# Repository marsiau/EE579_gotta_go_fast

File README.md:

# EE579_gotta_go_fast
Repository for EE579 line avoiding car project.

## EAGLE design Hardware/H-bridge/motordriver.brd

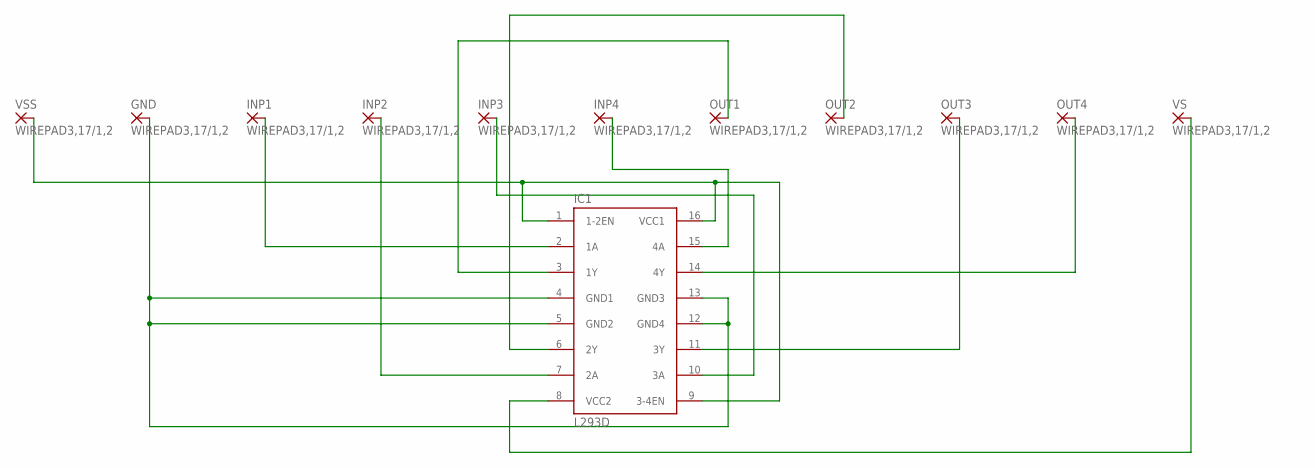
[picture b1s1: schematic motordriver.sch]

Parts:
GND: WIREPAD3,17/1,2; 3,17/1,2
IC1: L293D; DIL16
INP1, INP2, INP3, INP4: WIREPAD3,17/1,2; 3,17/1,2
OUT1, OUT2, OUT3, OUT4: WIREPAD3,17/1,2; 3,17/1,2
VS: WIREPAD3,17/1,2; 3,17/1,2
VSS: WIREPAD3,17/1,2; 3,17/1,2

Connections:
unnamed: IC1.8 (VCC2), VS.1
unnamed: IC1.1 (1-2EN), IC1.9 (3-4EN), IC1.16 (VCC1), VSS.1
unnamed: IC1.15 (4A), INP4.1
unnamed: IC1.14 (4Y), OUT4.1
unnamed: GND.1, IC1.4 (GND1), IC1.5 (GND2), IC1.12 (GND4), IC1.13 (GND3)
unnamed: IC1.11 (3Y), OUT3.1
unnamed: IC1.10 (3A), INP3.1
unnamed: IC1.2 (1A), INP1.1
unnamed: IC1.7 (2A), INP2.1
unnamed: IC1.3 (1Y), OUT1.1
unnamed: IC1.6 (2Y), OUT2.1

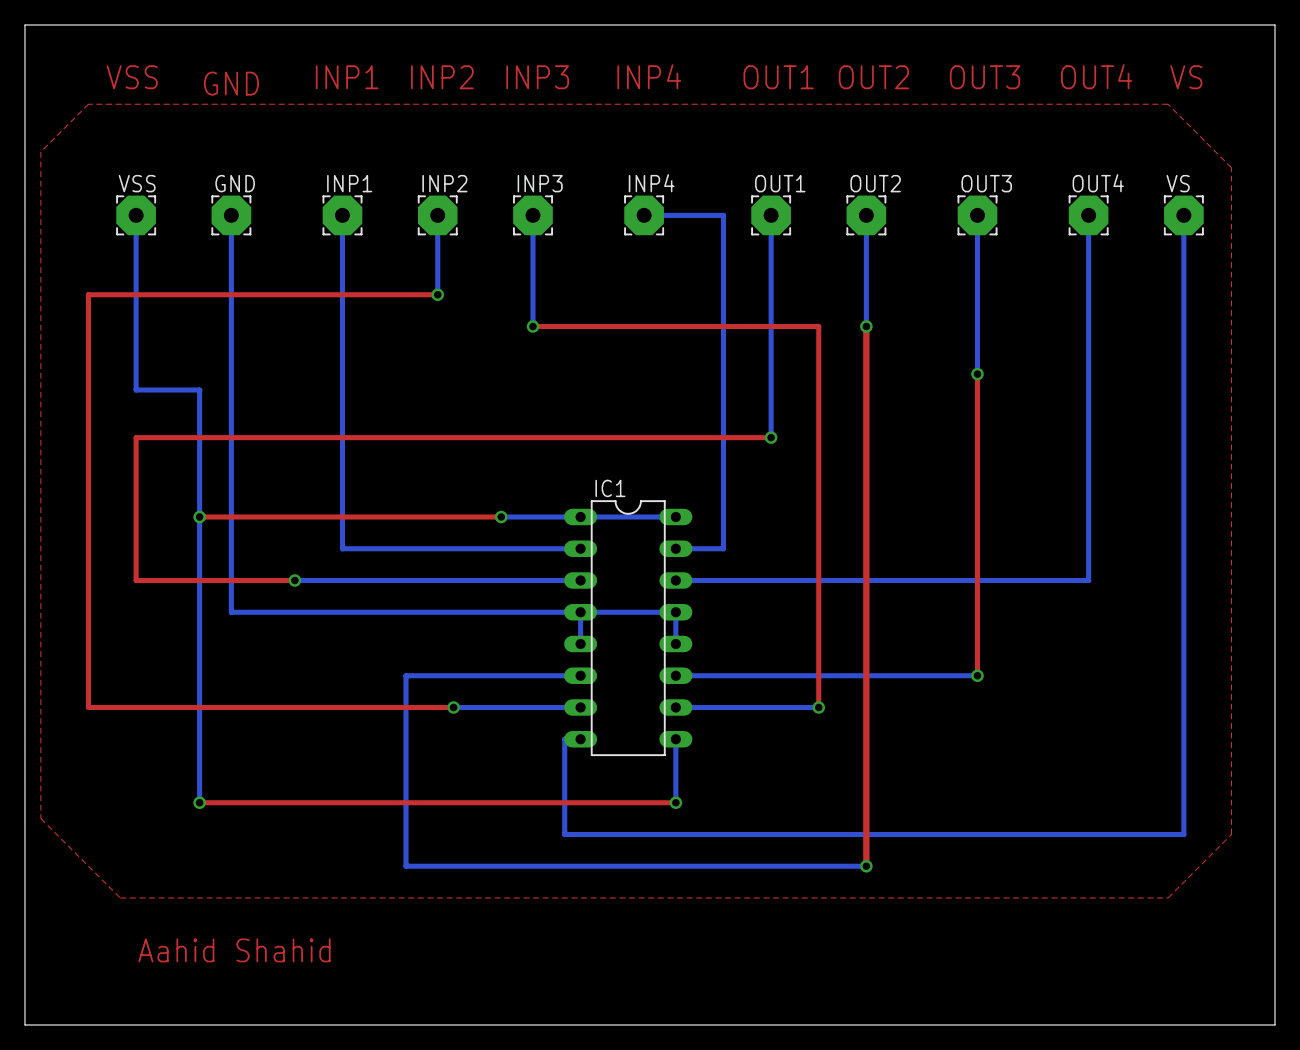
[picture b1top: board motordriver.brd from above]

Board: 2 copper layers, 100.0 x 80.0 mm, 12 parts (0 on the bottom side), 11 nets.

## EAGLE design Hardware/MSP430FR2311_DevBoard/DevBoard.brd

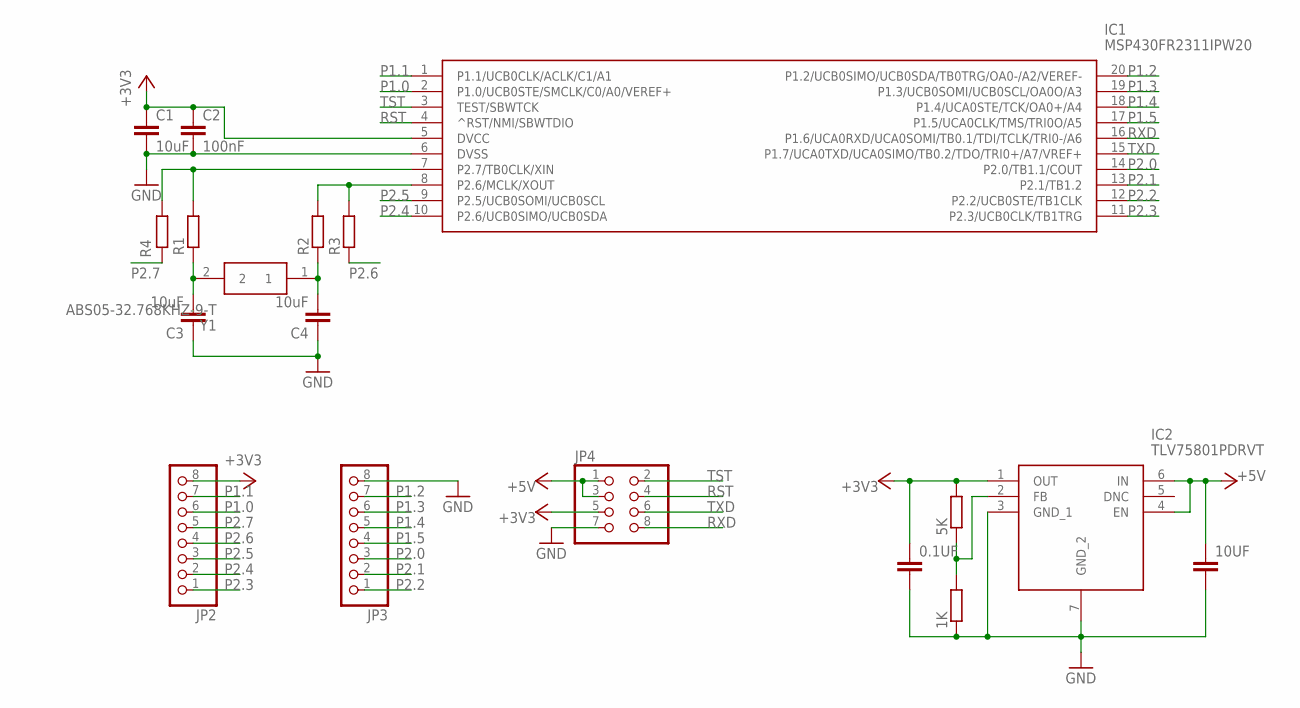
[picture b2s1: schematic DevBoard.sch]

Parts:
0.1UF, 10UF: C-EUC0805K; C0805K
1K, 5K: R-EU_R0805; R0805
C1, C3, C4: 10uF; C0805K
C2: 100nF; C0805K
IC1: MSP430FR2311IPW20; SOP65P640X120-20N
IC2: TLV75801PDRVT; SON65P200X200X80-7N
JP2, JP3: PINHD-1X8; 1X08
JP4: PINHD-2X4; 2X04
R1, R2, R3, R4: R-EU_R0402; R0402
Y1: ABS05-32.768KHZ-9-T; ABS05

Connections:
+3V3: 0.1UF.1, 5K.2, C1.1, C2.1, IC1.5 (DVCC), IC2.1 (OUT), JP2.8, JP4.5
+5V: 10UF.1, IC2.4 (EN), IC2.6 (IN), JP4.1, JP4.3
GND: 0.1UF.2, 1K.1, 10UF.2, C1.2, C2.2, C3.1, C4.1, IC1.6 (DVSS), IC2.3 (GND_1), IC2.7 (GND_2), JP3.8, JP4.7
unnamed: C3.2, R1.1, Y1.2
unnamed: C4.2, R2.1, Y1.1
unnamed: IC1.7 (P2.7/TB0CLK/XIN), R1.2, R4.1
unnamed: IC1.8 (P2.6/MCLK/XOUT), R2.2, R3.2
unnamed: 1K.2, 5K.1, IC2.2 (FB)
P1.0: IC1.2 (P1.0/UCB0STE/SMCLK/C0/A0/VEREF+), JP2.6
P1.1: IC1.1 (P1.1/UCB0CLK/ACLK/C1/A1), JP2.7
P1.2: IC1.20 (P1.2/UCB0SIMO/UCB0SDA/TB0TRG/OA0-/A2/VE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), JP3.7
P1.3: IC1.19 (P1.3/UCB0SOMI/UCB0SCL/OA0O/A3), JP3.6
P1.4: IC1.18 (P1.4/UCA0STE/TCK/OA0+/A4), JP3.5
P1.5: IC1.17 (P1.5/UCA0CLK/TMS/TRI0O/A5), JP3.4
P2.0: IC1.14 (P2.0/TB1.1/COUT), JP3.3
P2.1: IC1.13 (P2.1/TB1.2), JP3.2
P2.2: IC1.12 (P2.2/UCB0STE/TB1CLK), JP3.1
P2.3: IC1.11 (P2.3/UCB0CLK/TB1TRG), JP2.1
P2.4: IC1.10 (P2.6/UCB0SIMO/UCB0SDA), JP2.2
P2.5: IC1.9 (P2.5/UCB0SOMI/UCB0SCL), JP2.3
P2.6: JP2.4, R3.1
P2.7: JP2.5, R4.2
RST: IC1.4 (^RST/NMI/SBWTDIO), JP4.4
RXD: IC1.16 (P1.6/UCA0RXD/UCA0SOMI/TB0.1/TDI/TCLK/TR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), JP4.8
TST: IC1.3 (TEST/SBWTCK), JP4.2
TXD: IC1.15 (P1.7/UCA0TXD/UCA0SIMO/TB0.2/TDO/TRI0+/A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), JP4.6

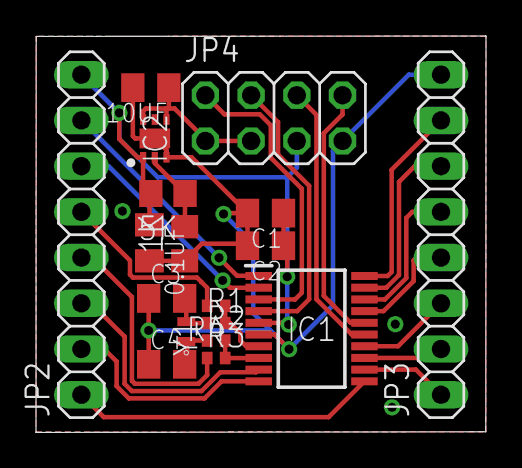
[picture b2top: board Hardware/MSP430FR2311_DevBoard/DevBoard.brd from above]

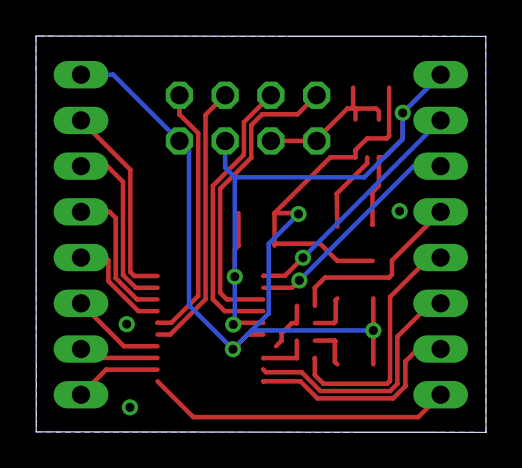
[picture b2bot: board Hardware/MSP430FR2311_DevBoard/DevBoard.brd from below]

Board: 2 copper layers, 25.0 x 22.0 mm, 26 parts (2 on the bottom side), 26 nets.

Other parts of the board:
U$1, U$2, U$3, U$4, U$5, U$7, U$8, U$9: METRIC_15

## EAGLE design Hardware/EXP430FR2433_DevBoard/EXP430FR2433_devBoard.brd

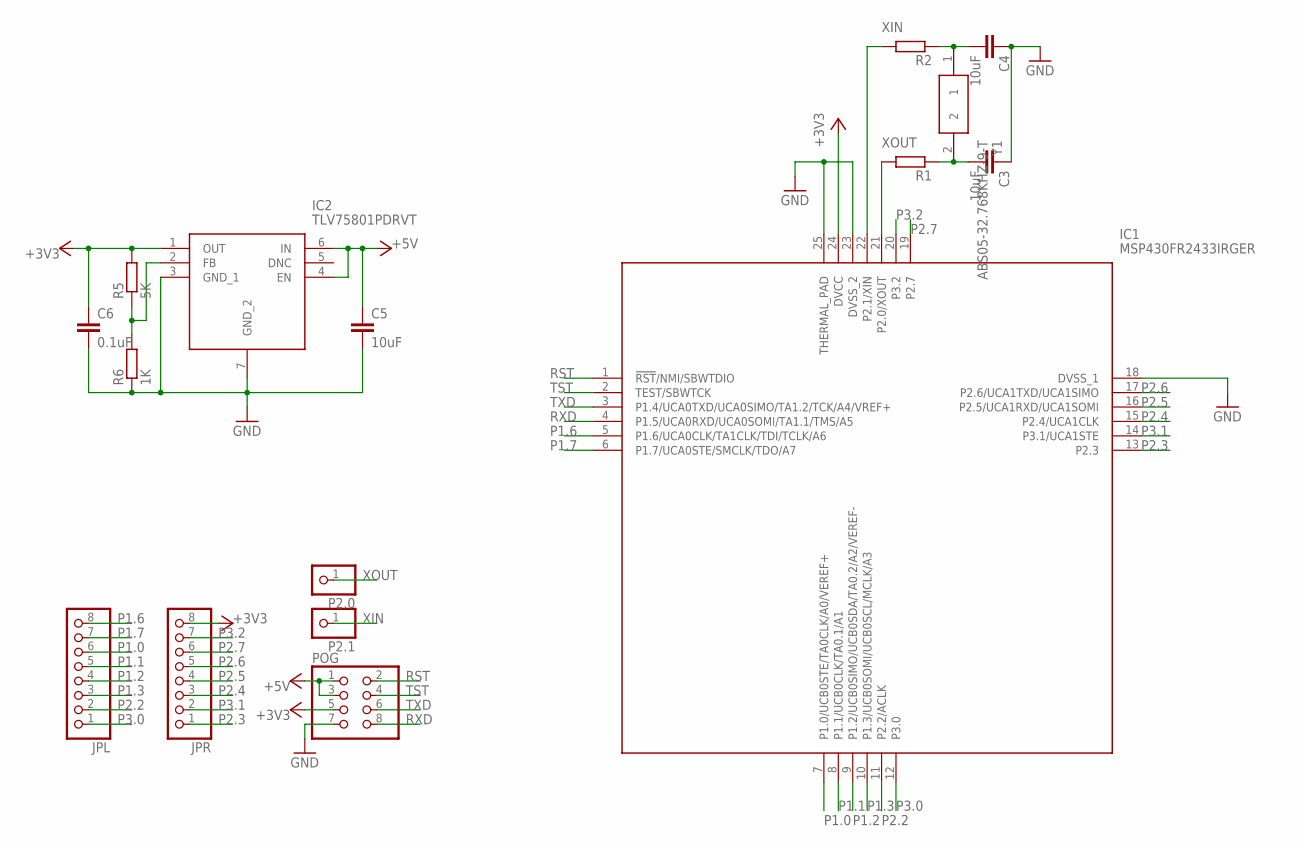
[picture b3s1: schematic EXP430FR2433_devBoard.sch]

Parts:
C3, C4, C5: 10uF; C0805K
C6: 0.1uF; C0805K
IC1: MSP430FR2433IRGER; QFN50P400X400X100-25N
IC2: TLV75801PDRVT; SON65P200X200X80-7N
JPL: PINHD-1X8; 1X08
JPR: PINHD-1X8; 1X08
P2.0, P2.1: PINHD-1X1; 1X01
POG: PINHD-2X4; 2X04
R1, R2: R-EU_R0402; R0402
R5: 5K; R0805
R6: 1K; R0805
Y1: ABS05-32.768KHZ-9-T; ABS05

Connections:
+3V3: C6.1, IC1.24 (DVCC), IC2.1 (OUT), JPR.8, POG.5, R5.2
+5V: C5.1, IC2.4 (EN), IC2.6 (IN), POG.1, POG.3
GND: C3.1, C4.1, C5.2, C6.2, IC1.18 (DVSS_1), IC1.23 (DVSS_2), IC1.25 (THERMAL_PAD), IC2.3 (GND_1), IC2.7 (GND_2), POG.7, R6.1
unnamed: C3.2, R1.1, Y1.2
unnamed: C4.2, R2.1, Y1.1
unnamed: IC2.2 (FB), R5.1, R6.2
P1.0: IC1.7 (P1.0/UCB0STE/TA0CLK/A0/VEREF+), JPL.6
P1.1: IC1.8 (P1.1/UCB0CLK/TA0.1/A1), JPL.5
P1.2: IC1.9 (P1.2/UCB0SIMO/UCB0SDA/TA0.2/A2/VEREF-), JPL.4
P1.3: IC1.10 (P1.3/UCB0SOMI/UCB0SCL/MCLK/A3), JPL.3
P1.6: IC1.5 (P1.6/UCA0CLK/TA1CLK/TDI/TCLK/A6), JPL.8
P1.7: IC1.6 (P1.7/UCA0STE/SMCLK/TDO/A7), JPL.7
P2.2: IC1.11 (P2.2/ACLK), JPL.2
P2.3: IC1.13 (P2.3), JPR.1
P2.4: IC1.15 (P2.4/UCA1CLK), JPR.3
P2.5: IC1.16 (P2.5/UCA1RXD/UCA1SOMI), JPR.4
P2.6: IC1.17 (P2.6/UCA1TXD/UCA1SIMO), JPR.5
P2.7: IC1.19 (P2.7), JPR.6
P3.0: IC1.12 (P3.0), JPL.1
P3.1: IC1.14 (P3.1/UCA1STE), JPR.2
P3.2: IC1.20 (P3.2), JPR.7
RST: IC1.1 (!RST!/NMI/SBWTDIO), POG.2
RXD: IC1.4 (P1.5/UCA0RXD/UCA0SOMI/TA1.1/TMS/A5), POG.8
TST: IC1.2 (TEST/SBWTCK), POG.4
TXD: IC1.3 (P1.4/UCA0TXD/UCA0SIMO/TA1.2/TCK/A4/VREF+), POG.6
XIN: IC1.22 (P2.1/XIN), P2.1.1, R2.2
XOUT: IC1.21 (P2.0/XOUT), P2.0.1, R1.2

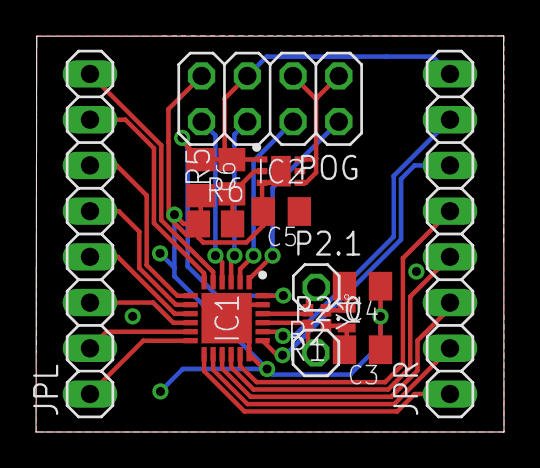
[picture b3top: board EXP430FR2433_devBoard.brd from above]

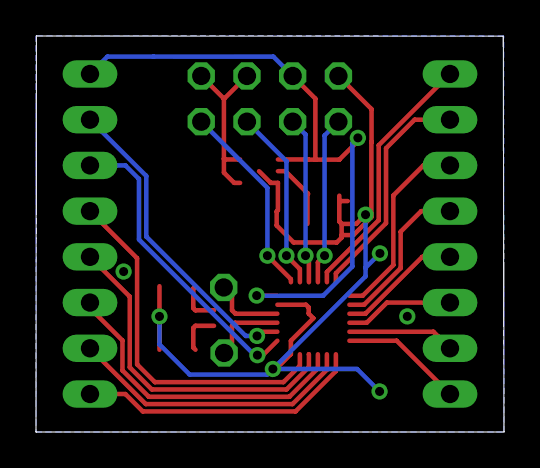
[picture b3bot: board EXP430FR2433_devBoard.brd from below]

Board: 2 copper layers, 26.0 x 22.0 mm, 23 parts (6 on the bottom side), 27 nets.

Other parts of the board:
U$1, U$2, U$3, U$4, U$5, U$6, U$7: METRIC_15

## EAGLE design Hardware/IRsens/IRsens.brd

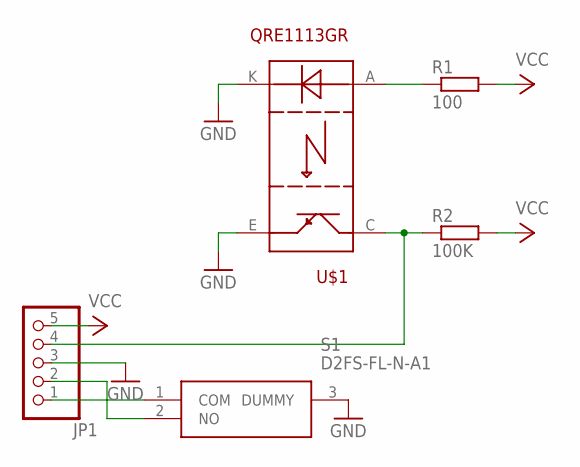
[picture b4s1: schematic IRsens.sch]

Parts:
JP1: PINHD-1X5; 1X05
R1: 100; R0805
R2: 100K; R0805
S1: D2FS-FL-N-A1
U$1: QRE1113GR; 4LEADSMD

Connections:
GND: JP1.3, S1.3 (DUMMY), U$1.E, U$1.K
unnamed: R1.1, U$1.A
unnamed: JP1.4, R2.1, U$1.C
unnamed: JP1.2, S1.2 (NO)
unnamed: JP1.1, S1.1 (COM)
VCC: JP1.5, R1.2, R2.2

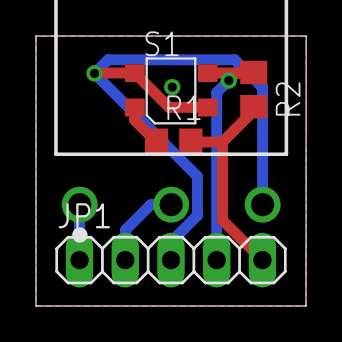
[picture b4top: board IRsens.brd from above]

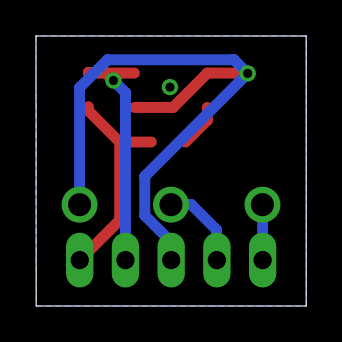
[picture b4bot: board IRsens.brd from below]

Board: 2 copper layers, 15.0 x 15.0 mm, 10 parts (3 on the bottom side), 6 nets.

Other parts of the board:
U$2, U$3, U$4, U$5, U$6: METRIC_15

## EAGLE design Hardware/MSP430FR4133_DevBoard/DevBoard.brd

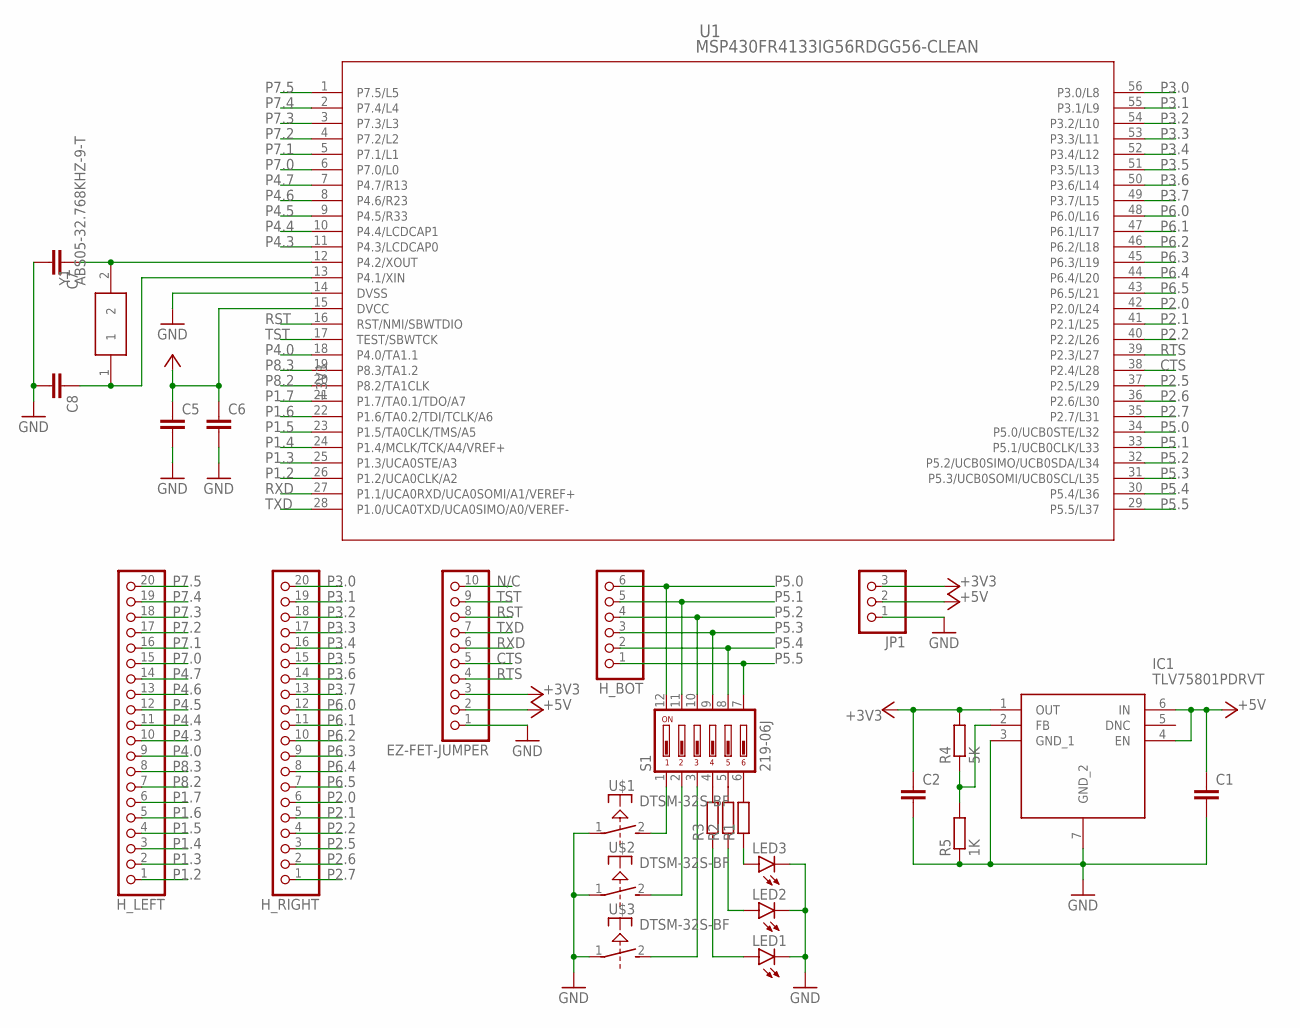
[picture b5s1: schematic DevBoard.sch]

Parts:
C1, C2, C5, C6, C7, C8: C-EUC0805K; C0805K
EZ-FET-JUMPER: PINHD-1X10; 1X10
H_BOT: PINHD-1X6; 1X06
H_LEFT: PINHD-1X20; 1X20
H_RIGHT: PINHD-1X20; 1X20
IC1: TLV75801PDRVT; SON65P200X200X80-7N
JP1: PINHD-1X3; 1X03
LED1, LED2, LED3: LEDCHIP-LED0805; CHIP-LED0805
R1, R2, R3: R-EU_R0805; R0805
R4: 5K; R0805
R5: 1K; R0805
S1: 219-06J; CTS-219-06J
U1: MSP430FR4133IG56RDGG56-CLEAN; DGG56_CLEAN
U$1, U$2, U$3: DTSM-32S-BF; DTSM32SBF
Y1: ABS05-32.768KHZ-9-T; ABS05

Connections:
+3V3: C2.1, C5.1, C6.1, EZ-FET-JUMPER.3, IC1.1 (OUT), JP1.3, R4.2, U1.15 (DVCC)
+5V: C1.1, EZ-FET-JUMPER.2, IC1.4 (EN), IC1.6 (IN), JP1.2
CTS: EZ-FET-JUMPER.5, U1.38 (P2.4/L28)
GND: C1.2, C2.2, C5.2, C6.2, C7.2, C8.2, EZ-FET-JUMPER.1, IC1.3 (GND_1), IC1.7 (GND_2), JP1.1, LED1.C, LED2.C, LED3.C, R5.1, U1.14 (DVSS), U$1.1, U$2.1, U$3.1
unnamed: R1.2, S1.6
unnamed: R2.2, S1.5
unnamed: R3.2, S1.4
unnamed: LED1.A, R3.1
unnamed: LED2.A, R2.1
unnamed: LED3.A, R1.1
unnamed: S1.1, U$1.2 (S)
unnamed: S1.2, U$2.2 (S)
unnamed: S1.3, U$3.2 (S)
unnamed: IC1.2 (FB), R4.1, R5.2
unnamed: C8.1, U1.13 (P4.1/XIN), Y1.1
unnamed: C7.1, U1.12 (P4.2/XOUT), Y1.2
N/C: EZ-FET-JUMPER.10
P1.2: H_LEFT.1, U1.26 (P1.2/UCA0CLK/A2)
P1.3: H_LEFT.2, U1.25 (P1.3/UCA0STE/A3)
P1.4: H_LEFT.3, U1.24 (P1.4/MCLK/TCK/A4/VREF+)
P1.5: H_LEFT.4, U1.23 (P1.5/TA0CLK/TMS/A5)
P1.6: H_LEFT.5, U1.22 (P1.6/TA0.2/TDI/TCLK/A6)
P1.7: H_LEFT.6, U1.21 (P1.7/TA0.1/TDO/A7)
P2.0: H_RIGHT.6, U1.42 (P2.0/L24)
P2.1: H_RIGHT.5, U1.41 (P2.1/L25)
P2.2: H_RIGHT.4, U1.40 (P2.2/L26)
P2.5: H_RIGHT.3, U1.37 (P2.5/L29)
P2.6: H_RIGHT.2, U1.36 (P2.6/L30)
P2.7: H_RIGHT.1, U1.35 (P2.7/L31)
P3.0: H_RIGHT.20, U1.56 (P3.0/L8)
P3.1: H_RIGHT.19, U1.55 (P3.1/L9)
P3.2: H_RIGHT.18, U1.54 (P3.2/L10)
P3.3: H_RIGHT.17, U1.53 (P3.3/L11)
P3.4: H_RIGHT.16, U1.52 (P3.4/L12)
P3.5: H_RIGHT.15, U1.51 (P3.5/L13)
P3.6: H_RIGHT.14, U1.50 (P3.6/L14)
P3.7: H_RIGHT.13, U1.49 (P3.7/L15)
P4.0: H_LEFT.9, U1.18 (P4.0/TA1.1)
P4.3: H_LEFT.10, U1.11 (P4.3/LCDCAP0)
P4.4: H_LEFT.11, U1.10 (P4.4/LCDCAP1)
P4.5: H_LEFT.12, U1.9 (P4.5/R33)
P4.6: H_LEFT.13, U1.8 (P4.6/R23)
P4.7: H_LEFT.14, U1.7 (P4.7/R13)
P5.0: H_BOT.6, S1.12, U1.34 (P5.0/UCB0STE/L32)
P5.1: H_BOT.5, S1.11, U1.33 (P5.1/UCB0CLK/L33)
P5.2: H_BOT.4, S1.10, U1.32 (P5.2/UCB0SIMO/UCB0SDA/L34)
P5.3: H_BOT.3, S1.9, U1.31 (P5.3/UCB0SOMI/UCB0SCL/L35)
P5.4: H_BOT.2, S1.8, U1.30 (P5.4/L36)
P5.5: H_BOT.1, S1.7, U1.29 (P5.5/L37)
P6.0: H_RIGHT.12, U1.48 (P6.0/L16)
P6.1: H_RIGHT.11, U1.47 (P6.1/L17)
P6.2: H_RIGHT.10, U1.46 (P6.2/L18)
P6.3: H_RIGHT.9, U1.45 (P6.3/L19)
P6.4: H_RIGHT.8, U1.44 (P6.4/L20)
P6.5: H_RIGHT.7, U1.43 (P6.5/L21)
P7.0: H_LEFT.15, U1.6 (P7.0/L0)
P7.1: H_LEFT.16, U1.5 (P7.1/L1)
P7.2: H_LEFT.17, U1.4 (P7.2/L2)
P7.3: H_LEFT.18, U1.3 (P7.3/L3)
P7.4: H_LEFT.19, U1.2 (P7.4/L4)
P7.5: H_LEFT.20, U1.1 (P7.5/L5)
P8.2: H_LEFT.7, U1.20 (P8.2/TA1CLK)
P8.3: H_LEFT.8, U1.19 (P8.3/TA1.2)
RST: EZ-FET-JUMPER.8, U1.16 (RST/NMI/SBWTDIO)
RTS: EZ-FET-JUMPER.4, U1.39 (P2.3/L27)
RXD: EZ-FET-JUMPER.6, U1.27 (P1.1/UCA0RXD/UCA0SOMI/A1/VEREF+)
TST: EZ-FET-JUMPER.9, U1.17 (TEST/SBWTCK)
TXD: EZ-FET-JUMPER.7, U1.28 (P1.0/UCA0TXD/UCA0SIMO/A0/VEREF-)

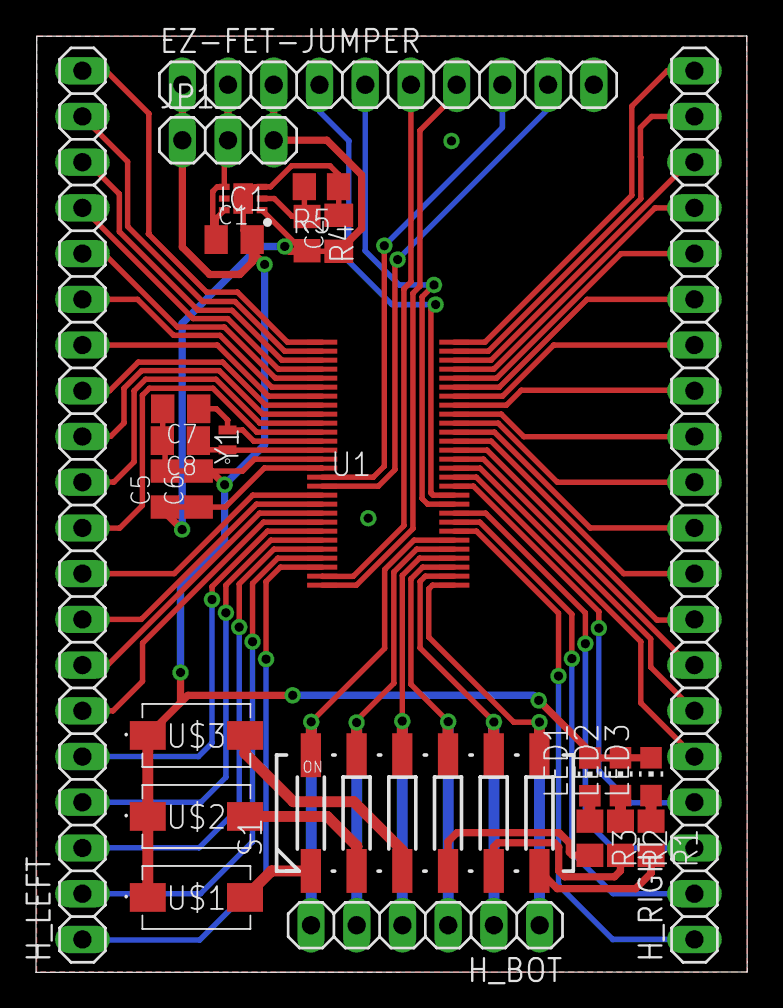
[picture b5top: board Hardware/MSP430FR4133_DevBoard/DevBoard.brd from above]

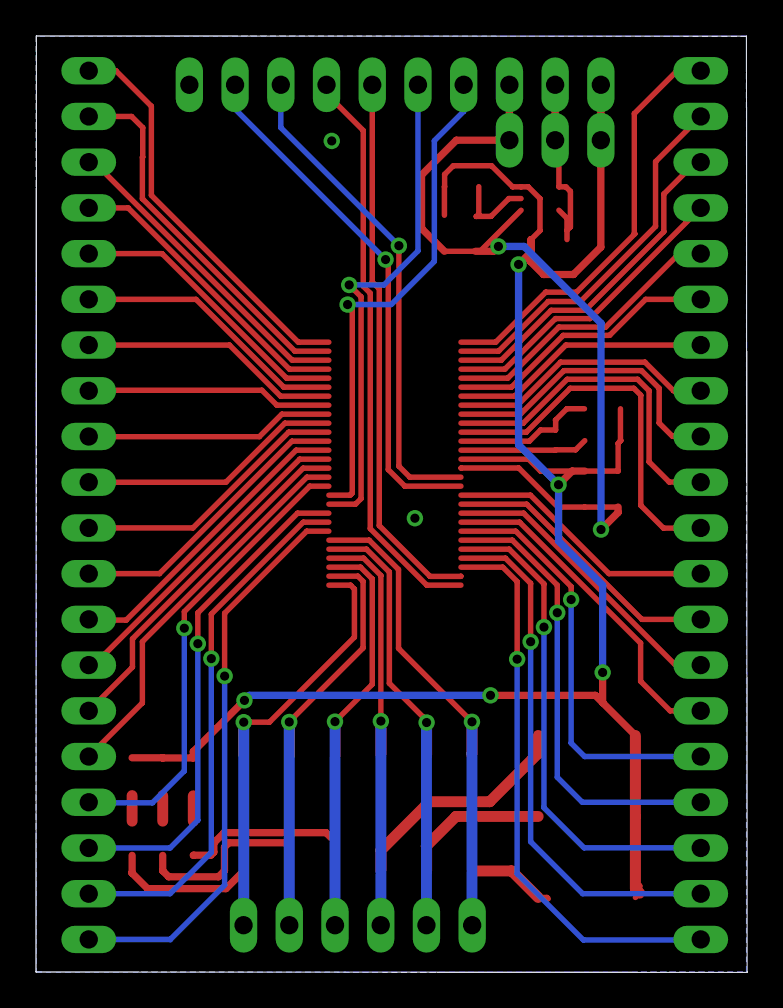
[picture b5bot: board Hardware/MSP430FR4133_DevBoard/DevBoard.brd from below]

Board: 2 copper layers, 39.5 x 52.0 mm, 29 parts (2 on the bottom side), 67 nets.

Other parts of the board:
U$4, U$5, U$6: METRIC_15

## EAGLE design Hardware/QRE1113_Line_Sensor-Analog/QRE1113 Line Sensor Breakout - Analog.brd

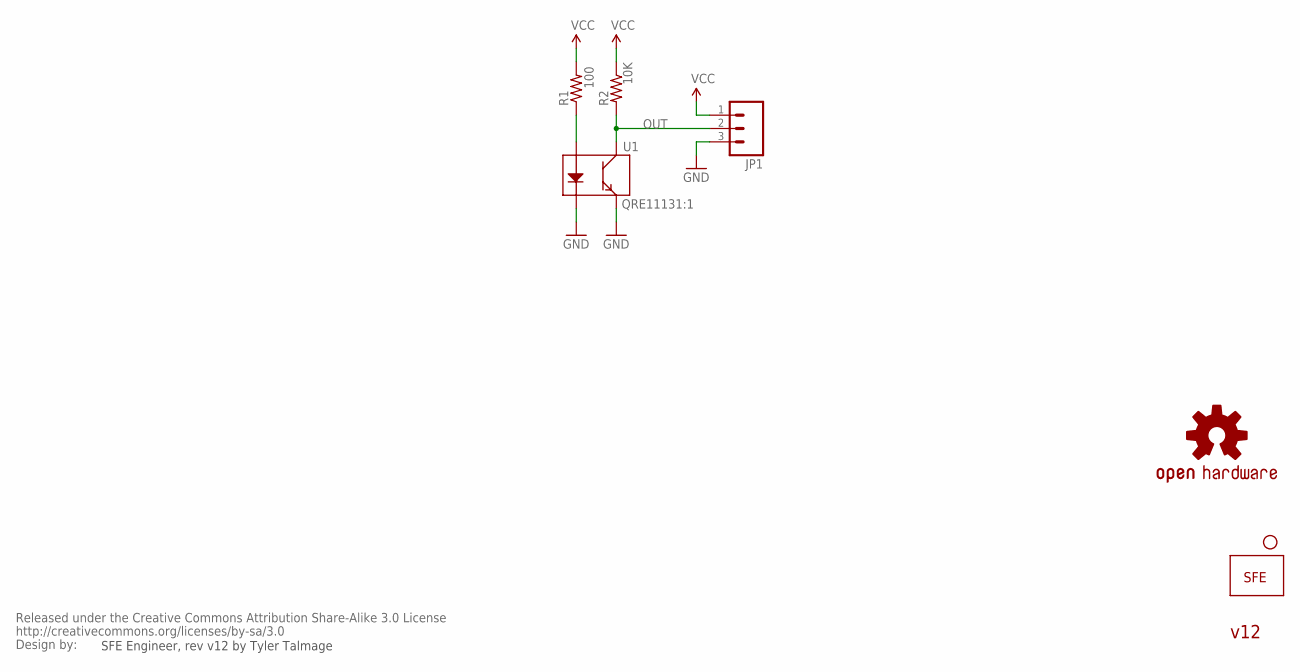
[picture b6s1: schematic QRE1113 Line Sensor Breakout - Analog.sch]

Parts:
CC_TEXT1: CREATIVE_COMMONS
JP1: M03PTH; 1X03
JP2: LOGO-SFESK; SFE-LOGO-FLAME
JP3: STAND-OFF
R1: 100; 0603-RES
R2: 10K; 0603-RES
U1: QRE11131:1; QRE1113-1:1
U$1: OSHW-LOGOS; OSHW-LOGO-S

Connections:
GND: JP1.3, U1.2 (K), U1.4 (E)
unnamed: R1.1, U1.1 (A)
OUT: JP1.2, R2.2, U1.3 (C)
VCC: JP1.1, R1.2, R2.1

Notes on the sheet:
SFE Engineer, rev v12 by Tyler Talmage
v12

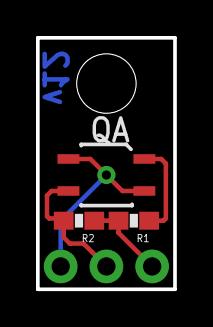
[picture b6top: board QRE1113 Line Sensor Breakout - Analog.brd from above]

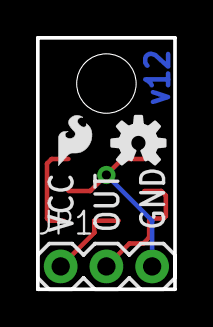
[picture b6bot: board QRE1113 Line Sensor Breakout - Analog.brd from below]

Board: 2 copper layers, 7.6 x 14.0 mm, 8 parts (3 on the bottom side), 4 nets.

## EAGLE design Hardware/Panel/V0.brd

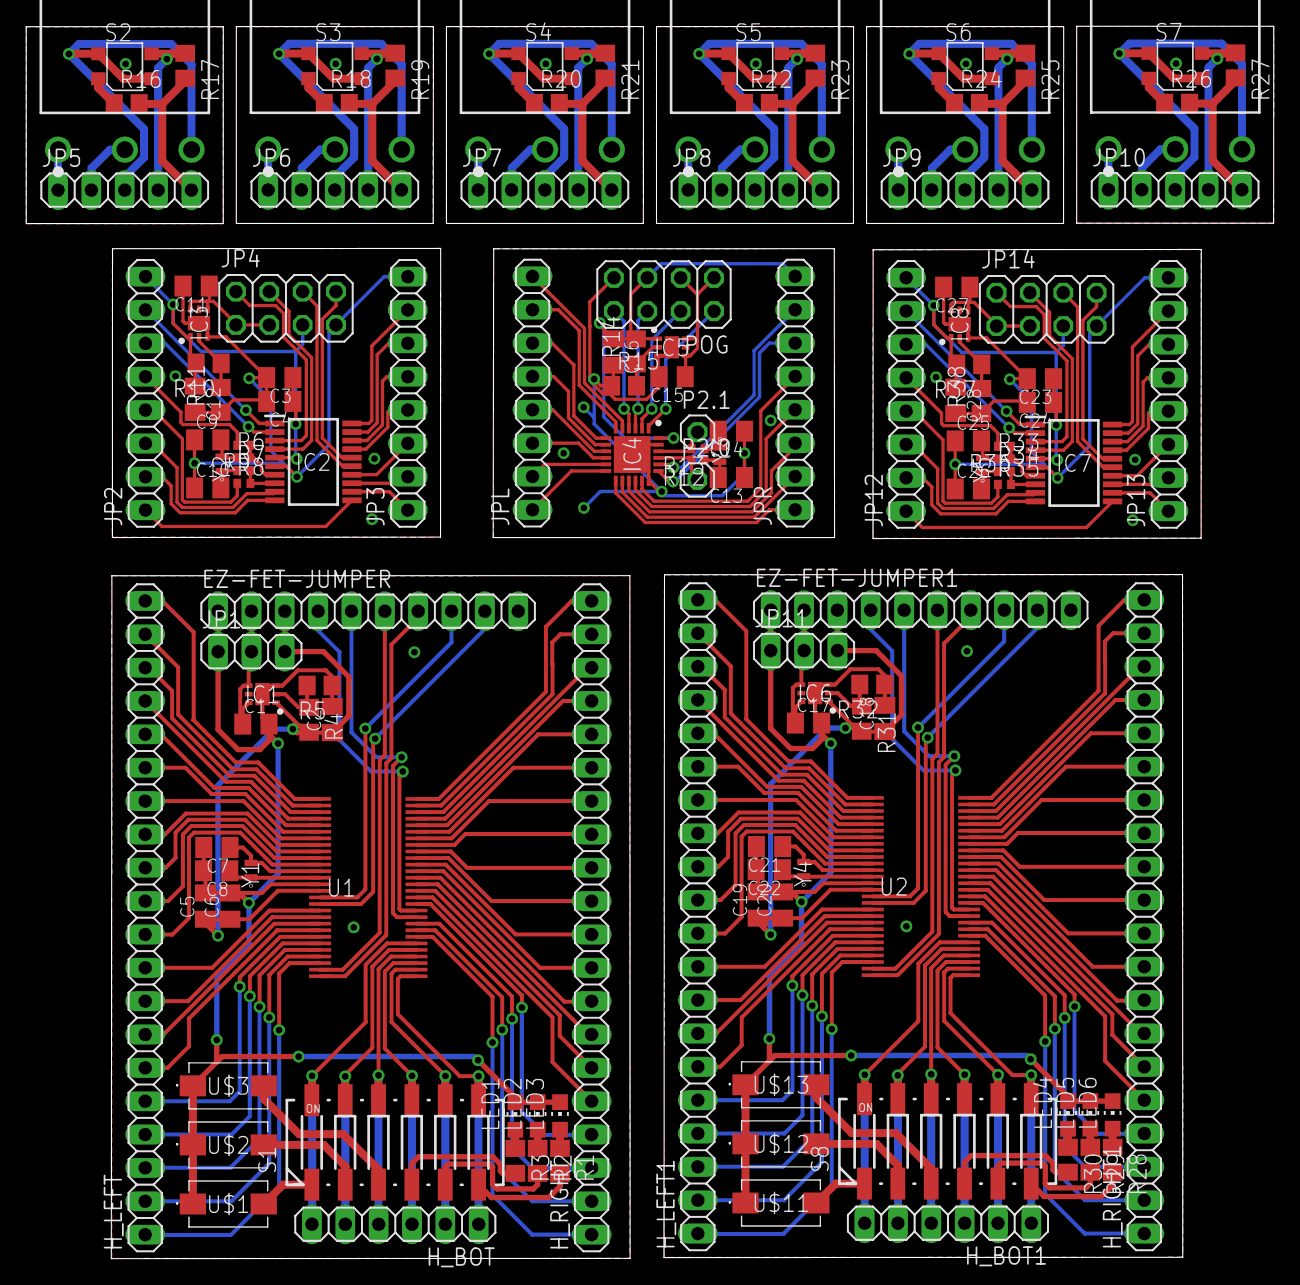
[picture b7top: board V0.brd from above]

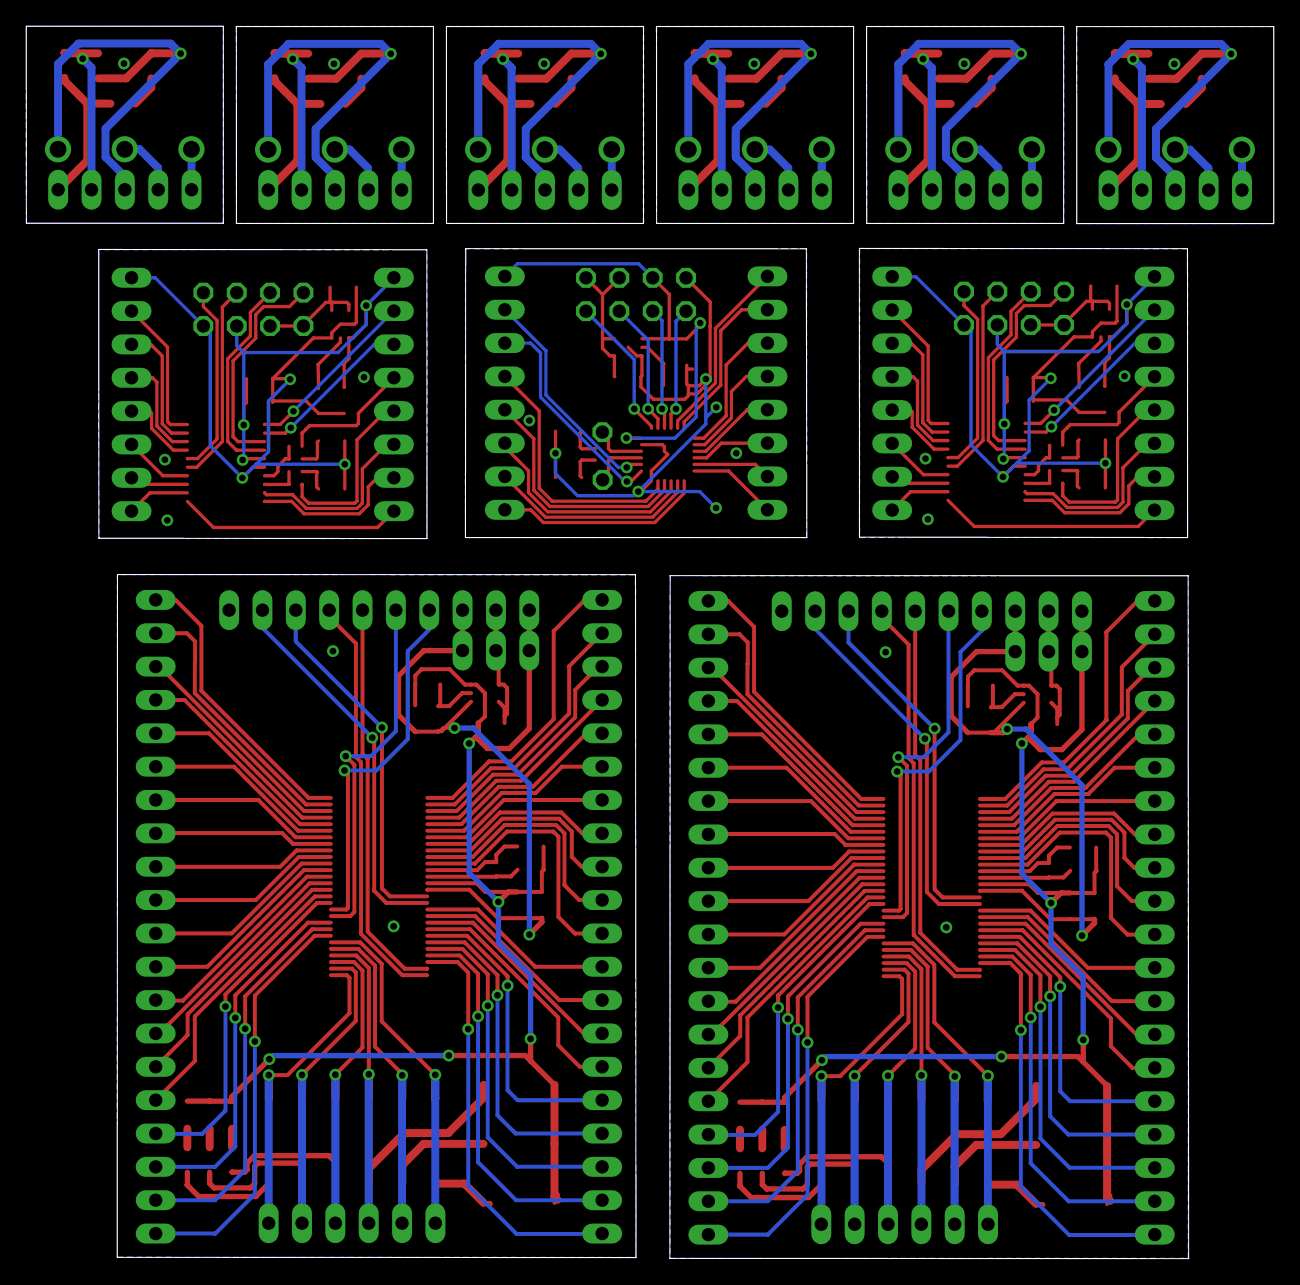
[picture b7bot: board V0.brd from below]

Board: 2 copper layers, 95.0 x 93.9 mm, 144 parts (5 on the bottom side), 249 nets.

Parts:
C1, C2, C5, C6, C7, C8, C11, C12, C15, C16, C17, C18, C19, C20, C21, C22, C27, C28: C0805K
C3, C9, C10, C13, C14, C23, C25, C26: 10uF; C0805K
C4, C24: 100nF; C0805K
E$1, E$2, E$3, E$4, E$5, E$6: METRIC_15
EZ-FET-JUMPER, EZ-FET-JUMPER1: 1X10
H_BOT, H_BOT1: 1X06
H_LEFT, H_LEFT1: 1X20
H_RIGHT, H_RIGHT1: 1X20
IC1, IC3, IC5, IC6, IC8: TLV75801PDRVT; SON65P200X200X80-7N
IC2, IC7: MSP430FR2311IPW20; SOP65P640X120-20N
IC4: MSP430FR2433IRGER; QFN50P400X400X100-25N
JP1, JP11: 1X03
JP2, JP3, JP12, JP13: 1X08
JP4, JP14: 2X04
JP5, JP6, JP7, JP8, JP9, JP10: 1X05
JPL: 1X08
JPR: 1X08
LED1, LED2, LED3, LED4, LED5, LED6: CHIP-LED0805
P2.0, P2.1: 1X01
POG: 2X04
R1, R2, R3, R4, R5, R10, R11, R14, R15, R28, R29, R30, R31, R32, R37, R38: R0805
R6, R7, R8, R9, R12, R13, R33, R34, R35, R36: R0402
R16, R18, R20, R22, R24, R26: 100; R0805
R17, R19, R21, R23, R25, R27: 100K; R0805
S1, S8: 219-06J; CTS-219-06J
S2, S3, S4, S5, S6, S7: D2FS-FL-N-A1
U1, U2: MSP430FR4133IG56RDGG56-CLEAN; DGG56_CLEAN
U$1, U$2, U$3, U$11, U$12, U$13: DTSM-32S-BF; DTSM32SBF
U$4, U$5, U$7, U$8: METRIC_15
U$6, U$9, U$10, U$15, U$21, U$27: QRE1113GR; 4LEADSMD
Y1, Y2, Y3, Y4, Y5: ABS05-32.768KHZ-9-T; ABS05

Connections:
+3V1: C3.1, C4.1, C12.1, IC2.5, IC3.1, JP2.8, JP4.5, R10.2
+3V2: C16.1, IC4.24, IC5.1, JPR.8, POG.5, R14.2
+3V3: C2.1, C5.1, C6.1, EZ-FET-JUMPER.3, IC1.1, JP1.3, R4.2, U1.15
+3V4: C18.1, C19.1, C20.1, EZ-FET-JUMPER1.3, IC6.1, JP11.3, R31.2, U2.15
+3V5: C23.1, C24.1, C28.1, IC7.5, IC8.1, JP12.8, JP14.5, R37.2
+5V: C1.1, EZ-FET-JUMPER.2, IC1.4, IC1.6, JP1.2
+5V1: C11.1, IC3.4, IC3.6, JP4.1, JP4.3
+5V2: C15.1, IC5.4, IC5.6, POG.1, POG.3
+5V3: C17.1, EZ-FET-JUMPER1.2, IC6.4, IC6.6, JP11.2
+5V4: C27.1, IC8.4, IC8.6, JP14.1, JP14.3
CTS: EZ-FET-JUMPER.5, U1.38
CTS1: EZ-FET-JUMPER1.5, U2.38
GND: C1.2, C2.2, C5.2, C6.2, C7.2, C8.2, EZ-FET-JUMPER.1, IC1.3, IC1.7, JP1.1, LED1.C, LED2.C, LED3.C, R5.1, U1.14, U$1.1, U$2.1, U$3.1
GND1: C3.2, C4.2, C9.1, C10.1, C11.2, C12.2, IC2.6, IC3.3, IC3.7, JP3.8, JP4.7, R11.1
GND2: C13.1, C14.1, C15.2, C16.2, IC4.18, IC4.23, IC4.25, IC5.3, IC5.7, POG.7, R15.1
GND3: JP5.3, S2.3, U$6.E, U$6.K
GND4: JP6.3, S3.3, U$9.E, U$9.K
GND5: JP7.3, S4.3, U$15.E, U$15.K
GND6: JP8.3, S5.3, U$21.E, U$21.K
GND7: JP9.3, S6.3, U$27.E, U$27.K
GND8: JP10.3, S7.3, U$10.E, U$10.K
GND9: C17.2, C18.2, C19.2, C20.2, C21.2, C22.2, EZ-FET-JUMPER1.1, IC6.3, IC6.7, JP11.1, LED4.C, LED5.C, LED6.C, R32.1, U2.14, U$11.1, U$12.1, U$13.1
GND10: C23.2, C24.2, C25.1, C26.1, C27.2, C28.2, IC7.6, IC8.3, IC8.7, JP13.8, JP14.7, R38.1
unnamed: R1.2, S1.6
unnamed: R2.2, S1.5
unnamed: R3.2, S1.4
unnamed: LED1.A, R3.1
unnamed: LED2.A, R2.1
unnamed: LED3.A, R1.1
unnamed: S1.1, U$1.2
unnamed: S1.2, U$2.2
unnamed: S1.3, U$3.2
unnamed: IC2.7, R6.2, R9.1
unnamed: IC2.8, R7.2, R8.2
unnamed: IC1.2, R4.1, R5.2
unnamed: IC3.2, R10.1, R11.2
unnamed: C8.1, U1.13, Y1.1
unnamed: C9.2, R6.1, Y2.2
unnamed: C7.1, U1.12, Y1.2
unnamed: C10.2, R7.1, Y2.1
unnamed: IC5.2, R14.1, R15.2
unnamed: C13.2, R12.1, Y3.2
unnamed: C14.2, R13.1, Y3.1
unnamed: R16.1, U$6.A
unnamed: JP5.4, R17.1, U$6.C
unnamed: JP5.2, S2.2
unnamed: JP5.1, S2.1
unnamed: R18.1, U$9.A
unnamed: JP6.4, R19.1, U$9.C
unnamed: JP6.2, S3.2
unnamed: JP6.1, S3.1
unnamed: R20.1, U$15.A
unnamed: JP7.4, R21.1, U$15.C
unnamed: JP7.2, S4.2
unnamed: JP7.1, S4.1
unnamed: R22.1, U$21.A
unnamed: JP8.4, R23.1, U$21.C
unnamed: JP8.2, S5.2
unnamed: JP8.1, S5.1
unnamed: R24.1, U$27.A
unnamed: JP9.4, R25.1, U$27.C
unnamed: JP9.2, S6.2
unnamed: JP9.1, S6.1
unnamed: R26.1, U$10.A
unnamed: JP10.4, R27.1, U$10.C
unnamed: JP10.2, S7.2
unnamed: JP10.1, S7.1
unnamed: C21.1, U2.12, Y4.2
unnamed: C22.1, U2.13, Y4.1
unnamed: LED4.A, R30.1
unnamed: LED5.A, R29.1
unnamed: LED6.A, R28.1
unnamed: S8.1, U$11.2
unnamed: S8.2, U$12.2
unnamed: S8.3, U$13.2
unnamed: IC6.2, R31.1, R32.2
unnamed: R28.2, S8.6
unnamed: R29.2, S8.5
unnamed: R30.2, S8.4
unnamed: IC7.7, R33.2, R36.1
unnamed: IC7.8, R34.2, R35.2
unnamed: IC8.2, R37.1, R38.2
unnamed: C25.2, R33.1, Y5.2
unnamed: C26.2, R34.1, Y5.1
P1.0: IC2.2, JP2.6
P1.1: IC2.1, JP2.7
P1.2: H_LEFT.1, U1.26
P1.3: H_LEFT.2, U1.25
P1.4: H_LEFT.3, U1.24
P1.5: H_LEFT.4, U1.23
P1.6: H_LEFT.5, U1.22
P1.7: H_LEFT.6, U1.21
P1.8: IC2.20, JP3.7
P1.9: IC2.19, JP3.6
P1.10: IC2.18, JP3.5
P1.11: IC2.17, JP3.4
P1.12: IC4.10, JPL.3
P1.13: IC4.9, JPL.4
P1.14: IC4.8, JPL.5
P1.15: IC4.7, JPL.6
P1.16: IC4.5, JPL.8
P1.17: IC4.6, JPL.7
P1.18: H_LEFT1.6, U2.21
P1.19: H_LEFT1.5, U2.22
P1.20: H_LEFT1.4, U2.23
P1.21: H_LEFT1.3, U2.24
P1.22: H_LEFT1.2, U2.25
P1.23: H_LEFT1.1, U2.26
P1.24: IC7.1, JP12.7
P1.25: IC7.2, JP12.6
P1.26: IC7.20, JP13.7
P1.27: IC7.19, JP13.6
P1.28: IC7.18, JP13.5
P1.29: IC7.17, JP13.4
P2.0: H_RIGHT.6, U1.42
P2.1: H_RIGHT.5, U1.41
P2.2: H_RIGHT.4, U1.40
P2.3: IC2.14, JP3.3
P2.4: IC2.13, JP3.2
P2.5: H_RIGHT.3, U1.37
P2.6: H_RIGHT.2, U1.36
P2.7: H_RIGHT.1, U1.35
P2.8: IC2.12, JP3.1
P2.9: JP2.5, R9.2
P2.10: JP2.4, R8.1
P2.11: IC2.9, JP2.3
P2.12: IC2.10, JP2.2
P2.13: IC2.11, JP2.1
P2.14: IC4.17, JPR.5
P2.15: IC4.16, JPR.4
P2.16: IC4.15, JPR.3
P2.17: IC4.13, JPR.1
P2.18: IC4.11, JPL.2
P2.19: IC4.19, JPR.6
P2.20: H_RIGHT1.6, U2.42
P2.21: H_RIGHT1.5, U2.41
P2.22: H_RIGHT1.4, U2.40
P2.23: H_RIGHT1.3, U2.37
P2.24: H_RIGHT1.2, U2.36
P2.25: H_RIGHT1.1, U2.35
P2.26: IC7.14, JP13.3
P2.27: IC7.13, JP13.2
P2.28: IC7.12, JP13.1
P2.29: JP12.5, R36.2
P2.30: JP12.4, R35.1
P2.31: IC7.9, JP12.3
P2.32: IC7.10, JP12.2
P2.33: IC7.11, JP12.1
P3.0: H_RIGHT.20, U1.56
P3.1: H_RIGHT.19, U1.55
P3.2: H_RIGHT.18, U1.54
P3.3: H_RIGHT.17, U1.53
P3.4: H_RIGHT.16, U1.52
P3.5: H_RIGHT.15, U1.51
P3.6: H_RIGHT.14, U1.50
P3.7: H_RIGHT.13, U1.49
P3.8: IC4.14, JPR.2
P3.9: IC4.12, JPL.1
P3.10: IC4.20, JPR.7
P3.11: H_RIGHT1.20, U2.56
P3.12: H_RIGHT1.19, U2.55
P3.13: H_RIGHT1.18, U2.54
P3.14: H_RIGHT1.17, U2.53
P3.15: H_RIGHT1.16, U2.52
P3.16: H_RIGHT1.15, U2.51
P3.17: H_RIGHT1.14, U2.50
P3.18: H_RIGHT1.13, U2.49
P4.0: H_LEFT.9, U1.18
P4.1: H_LEFT1.14, U2.7
P4.2: H_LEFT1.13, U2.8
P4.3: H_LEFT.10, U1.11
P4.4: H_LEFT.11, U1.10
P4.5: H_LEFT.12, U1.9
P4.6: H_LEFT.13, U1.8
P4.7: H_LEFT.14, U1.7
P4.8: H_LEFT1.12, U2.9
P4.9: H_LEFT1.11, U2.10
P4.10: H_LEFT1.10, U2.11
P4.11: H_LEFT1.9, U2.18
P5.0: H_BOT.6, S1.12, U1.34
P5.1: H_BOT.5, S1.11, U1.33
P5.2: H_BOT.4, S1.10, U1.32
P5.3: H_BOT.3, S1.9, U1.31
P5.4: H_BOT.2, S1.8, U1.30
P5.5: H_BOT.1, S1.7, U1.29
P5.6: H_BOT1.1, S8.7, U2.29
P5.7: H_BOT1.2, S8.8, U2.30
P5.8: H_BOT1.6, S8.12, U2.34
P5.9: H_BOT1.5, S8.11, U2.33
P5.10: H_BOT1.4, S8.10, U2.32
P5.11: H_BOT1.3, S8.9, U2.31
P6.0: H_RIGHT.12, U1.48
P6.1: H_RIGHT.11, U1.47
P6.2: H_RIGHT.10, U1.46
P6.3: H_RIGHT.9, U1.45
P6.4: H_RIGHT.8, U1.44
P6.5: H_RIGHT.7, U1.43
P6.6: H_RIGHT1.12, U2.48
P6.7: H_RIGHT1.11, U2.47
P6.8: H_RIGHT1.10, U2.46
P6.9: H_RIGHT1.9, U2.45
P6.10: H_RIGHT1.8, U2.44
P6.11: H_RIGHT1.7, U2.43
P7.0: H_LEFT.15, U1.6
P7.1: H_LEFT.16, U1.5
P7.2: H_LEFT.17, U1.4
P7.3: H_LEFT.18, U1.3
P7.4: H_LEFT.19, U1.2
P7.5: H_LEFT.20, U1.1
P7.6: H_LEFT1.20, U2.1
P7.7: H_LEFT1.18, U2.3
P7.8: H_LEFT1.19, U2.2
P7.9: H_LEFT1.17, U2.4
P7.10: H_LEFT1.16, U2.5
P7.11: H_LEFT1.15, U2.6
P8.1: H_LEFT1.8, U2.19
P8.2: H_LEFT.7, U1.20
P8.3: H_LEFT.8, U1.19
P8.4: H_LEFT1.7, U2.20
RST: EZ-FET-JUMPER.8, U1.16
RST1: IC2.4, JP4.4
RST2: IC4.1, POG.2
RST3: EZ-FET-JUMPER1.8, U2.16
RST4: IC7.4, JP14.4
RTS: EZ-FET-JUMPER.4, U1.39
RTS1: EZ-FET-JUMPER1.4, U2.39
RXD: EZ-FET-JUMPER.6, U1.27
RXD1: IC2.16, JP4.8
RXD2: IC4.4, POG.8
RXD3: EZ-FET-JUMPER1.6, U2.27
RXD4: IC7.16, JP14.8
TST: EZ-FET-JUMPER.9, U1.17
TST1: IC2.3, JP4.2
TST2: IC4.2, POG.4
TST3: EZ-FET-JUMPER1.9, U2.17
TST4: IC7.3, JP14.2
TXD: EZ-FET-JUMPER.7, U1.28
TXD1: IC2.15, JP4.6
TXD2: IC4.3, POG.6
TXD3: EZ-FET-JUMPER1.7, U2.28
TXD4: IC7.15, JP14.6
VCC: JP5.5, R16.2, R17.2
VCC1: JP6.5, R18.2, R19.2
VCC2: JP7.5, R20.2, R21.2
VCC3: JP8.5, R22.2, R23.2
VCC4: JP9.5, R24.2, R25.2
VCC5: JP10.5, R26.2, R27.2
XIN: IC4.22, P2.1.1, R13.2
XOUT: IC4.21, P2.0.1, R12.2

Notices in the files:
parts and their libraries:
ruler: BSD licence
© 2012 Janusz Kostorz (janusz.kostorz@gmail.com)
All rights reserved.
End of BSD licence
SparkFun-Aesthetics: Licensing: CC v3.0 Share-Alike You are welcome to use this library for commercial purposes.
SparkFun-Aesthetics: http://creativecommons.org/licenses/by-sa/3.0
